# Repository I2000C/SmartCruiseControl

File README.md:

# SmartCruiseControl

SmartCruiseControl is an embedded ESP32 project that implements cruise control using CAN Bus data, with vehicle state monitoring and ELM327 command emulation for the **Smart forfour 454** car

## Description

The software runs on an ESP32 using the Arduino framework and focuses on:

- Reading CAN Bus frames from a Smart vehicle.
- Estimating speed, RPM, distance, fuel level, and other critical vehicle parameters.
- Cruise control with PID, button-based enable/disable, and throttle override handling.
- Basic ELM327 emulation for OBD-II `01xx` and `22xx` command responses.
- Cruise control status indication using an LED.

## Key features

- CAN Bus listen-only mode (`TWAI_MODE_LISTEN_ONLY`) at 500 kbps.
- Support for reading the following key CAN IDs:
  - `0x09E` - total distance
  - `0x200` - speed
  - `0x208` - brake intensity and extra speed data
  - `0x210` - accelerator pedal position
  - `0x308` - engine RPM
  - `0x408` - fuel level
  - `0x416` - battery voltage
  - `0x423` - door status
  - `0x608` - refrigerant temperature and fuel rate
- Cruise control state machine with:
  - `STATE_OFF`
  - `STATE_ACTIVE`
  - `STATE_OVERRIDE`
- ELM327 interface over `Serial` with basic `AT`, `01`, and `22` command handling.

## Project structure

- `platformio.ini` - PlatformIO configuration for ESP32.
- `src/main.cpp` - main entry point and FreeRTOS task setup.
- `include/` - constants, state definitions, and shared headers.
- `lib/` - modular libraries:
  - `can/` - CAN bus reading and decoding.
  - `cruise_control/` - cruise control logic.
  - `elm327/` - ELM327 emulation and OBD response handling.
  - `fuel_range_estimator/` - fuel range estimation.
  - `indicator_led/` - PWM LED status indicator.
  - `pid_controller/` - generic PID controller.
  - `speed_estimator/` - speed estimation from CAN frames.
  - `throttle/` - throttle output and override management.
  - `buttons/` - analog button reading and cruise control button detection.
- `doc/` - CAN Bus reverse engineering documentation.
- `test/` - PlatformIO testing notes and setup.

## Requirements

See `requirements.md` file for required software and hardware

## How to build

See `how-to-build.md` file to build software and hardware

## Usage

- The system starts by creating FreeRTOS tasks for CAN reception, CAN processing, and ELM327 emulation.
- The indicator LED shows cruise control status:
  - off = cruise control disabled
  - full brightness = cruise control active
  - fading = throttle override active
- Cruise control buttons support `SET`, `RESUME`, and `CANCEL`.
- Pressing the accelerator while cruise control is active transitions the system to `STATE_OVERRIDE`.

## Notes

- The project is designed for the Smart Forfour 454 (2006) model, as described at the beginning of `doc/CAN bus reverse engineering.md`.
- With the necessary modifications, it could be adapted to other vehicles that use CAN Bus, electronic throttle, and physical brake/clutch switches.
- The implementation is based on CAN data documented in `doc/CAN bus reverse engineering.md`.
- The ESP32 pinout reference image is available at `doc/ESP32 pinout.png` and is used under Creative Commons BY-NC-ND via www.mischianti.org.

## Inspirations

This project was inspired by:

- [esp32_cruise_control](https://github.com/successdt/esp32_cruise_control)
- [autocruise](https://github.com/SantiagoDelEstero/autocruise)
- [esp32-elm327-cruise-control](https://github.com/ipepe-oss/esp32-elm327-cruise-control)

## License

See the `LICENSE` file for the project license terms.

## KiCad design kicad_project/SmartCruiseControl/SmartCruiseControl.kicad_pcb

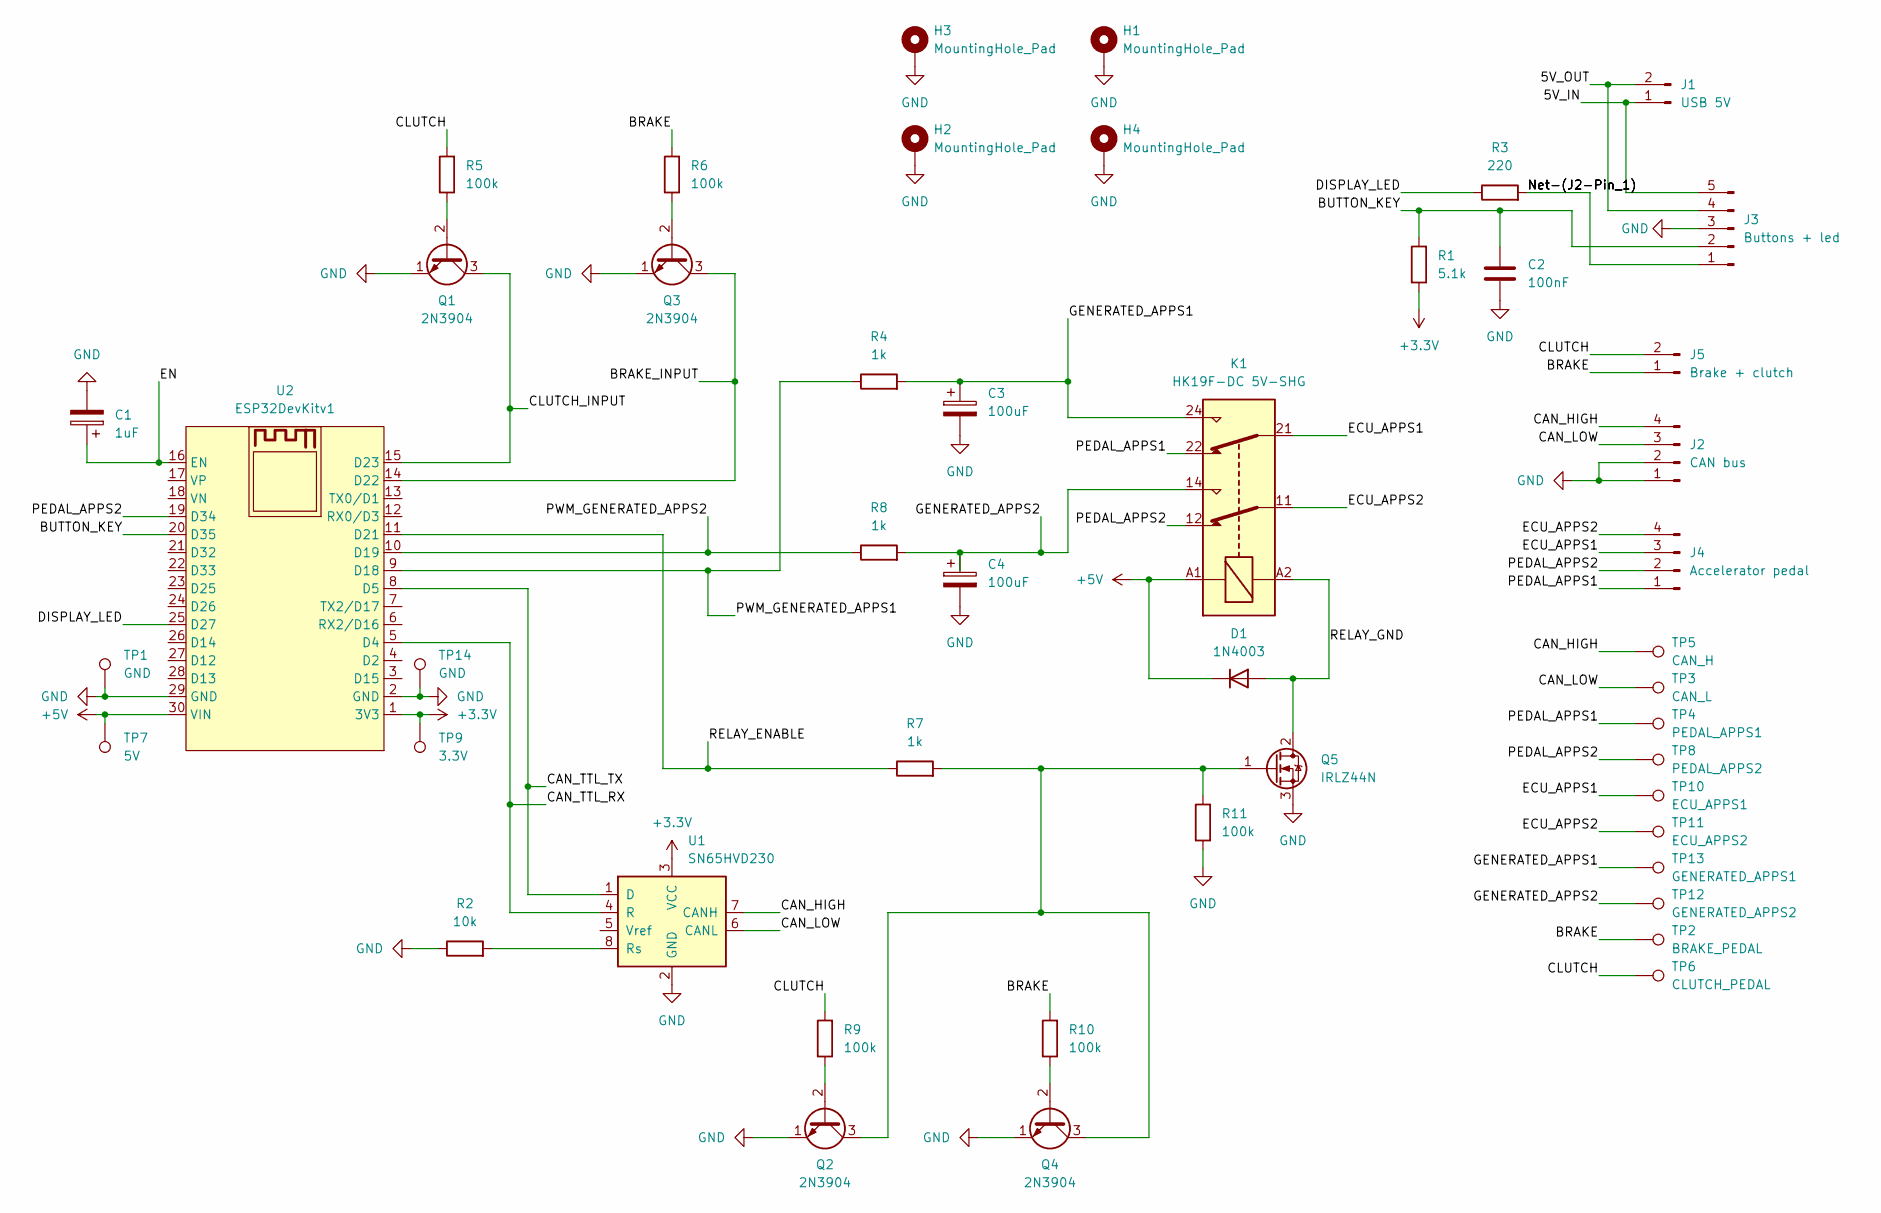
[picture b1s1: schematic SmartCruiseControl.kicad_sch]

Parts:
C1: 1uF; CP_Radial_D5.0mm_P2.00mm
C2: 100nF; C_Disc_D5.0mm_W2.5mm_P5.00mm
C3, C4: 100uF; CP_Radial_D5.0mm_P2.00mm
D1: 1N4003; D_DO-41_SOD81_P10.16mm_Horizontal
H1, H2, H3, H4: MountingHole_Pad; MountingHole_3.2mm_M3_Pad_Via
J1: USB 5V; JST_XH_B2B-XH-A_1x02_P2.50mm_Vertical
J2: CAN bus; JST_XH_B4B-XH-A_1x04_P2.50mm_Vertical
J3: Buttons + led; JST_XH_B5B-XH-A_1x05_P2.50mm_Vertical
J4: Accelerator pedal; JST_XH_B4B-XH-A_1x04_P2.50mm_Vertical
J5: Brake + clutch; JST_XH_B2B-XH-A_1x02_P2.50mm_Vertical
K1: HK19F-DC 5V-SHG; Relay_DPDT_Omron_G6A
Q1, Q2, Q3, Q4: 2N3904; TO-92_Inline
Q5: IRLZ44N; TO-220-3_Vertical
R1: 5.1k; R_Axial_DIN0207_L6.3mm_D2.5mm_P10.16mm_Horizontal
R2: 10k; R_Axial_DIN0207_L6.3mm_D2.5mm_P10.16mm_Horizontal
R3: 220; R_Axial_DIN0207_L6.3mm_D2.5mm_P10.16mm_Horizontal
R4, R7, R8: 1k; R_Axial_DIN0207_L6.3mm_D2.5mm_P10.16mm_Horizontal
R5, R6, R9, R10, R11: 100k; R_Axial_DIN0207_L6.3mm_D2.5mm_P10.16mm_Horizontal
TP1, TP14: GND; TestPoint_THTPad_2.0x2.0mm_Drill1.0mm
TP2: BRAKE_PEDAL; TestPoint_THTPad_D1.0mm_Drill0.5mm
TP3: CAN_L; TestPoint_THTPad_D1.0mm_Drill0.5mm
TP4: PEDAL_APPS1; TestPoint_THTPad_D1.0mm_Drill0.5mm
TP5: CAN_H; TestPoint_THTPad_D1.0mm_Drill0.5mm
TP6: CLUTCH_PEDAL; TestPoint_THTPad_D1.0mm_Drill0.5mm
TP7: 5V; TestPoint_THTPad_D2.0mm_Drill1.0mm
TP8: PEDAL_APPS2; TestPoint_THTPad_D1.0mm_Drill0.5mm
TP9: 3.3V; TestPoint_THTPad_D1.5mm_Drill0.7mm
TP10: ECU_APPS1; TestPoint_THTPad_D1.0mm_Drill0.5mm
TP11: ECU_APPS2; TestPoint_THTPad_D1.0mm_Drill0.5mm
TP12: GENERATED_APPS2; TestPoint_THTPad_D1.0mm_Drill0.5mm
TP13: GENERATED_APPS1; TestPoint_THTPad_D1.0mm_Drill0.5mm
U1: SN65HVD230; SOIC-8_3.9x4.9mm_P1.27mm
U2: ESP32DevKitv1

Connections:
+3.3V: R1.1, TP9.1 (1_1), U1.3 (VCC), U2.1 (3V3)
+5V: D1.1 (K), K1.A1, TP7.1 (1_1), U2.30 (VIN)
/5V_IN: J1.1, J3.5
/5V_OUT: J1.2, J3.4
/BRAKE: J5.1, R6.2, R10.2, TP2.1 (1_1)
/BRAKE_INPUT: Q3.3 (C), U2.14 (D22)
/BUTTON_KEY: C2.1, J3.2, R1.2, U2.20 (D35)
/CAN_HIGH: J2.4, TP5.1 (1_1), U1.7 (CANH)
/CAN_LOW: J2.3, TP3.1 (1_1), U1.6 (CANL)
/CAN_TTL_RX: U1.4 (R), U2.5 (D4)
/CAN_TTL_TX: U1.1 (D), U2.8 (D5)
/CLUTCH: J5.2, R5.2, R9.2, TP6.1 (1_1)
/CLUTCH_INPUT: Q1.3 (C), U2.15 (D23)
/DISPLAY_LED: R3.1, U2.25 (D27)
/ECU_APPS1: J4.3, K1.21, TP10.1 (1_1)
/ECU_APPS2: J4.4, K1.11, TP11.1 (1_1)
/EN: C1.1, U2.16 (EN)
/GENERATED_APPS1: C3.1, K1.24, R4.2, TP13.1 (1_1)
/GENERATED_APPS2: C4.1, K1.14, R8.2, TP12.1 (1_1)
/Net-(J2-Pin_1): J3.1, R3.2
/PEDAL_APPS1: J4.1, K1.22, TP4.1 (1_1)
/PEDAL_APPS2: J4.2, K1.12, TP8.1 (1_1), U2.19 (D34)
/PWM_GENERATED_APPS1: R4.1, U2.9 (D18)
/PWM_GENERATED_APPS2: R8.1, U2.10 (D19)
/RELAY_ENABLE: R7.1, U2.11 (D21)
/RELAY_GND: D1.2 (A), K1.A2, Q5.2 (D)
GND: C1.2, C2.2, C3.2, C4.2, H1.1 (1_1), H2.1 (1_1), H3.1 (1_1), H4.1 (1_1), J2.1, J2.2, J3.3, Q1.1 (E), Q2.1 (E), Q3.1 (E), Q4.1 (E), Q5.3 (S), R2.1, R11.1, TP1.1 (1_1), TP14.1 (1_1), U1.2 (GND), U2.2 (GND), U2.29 (GND)
unnamed: Q1.2 (B), R5.1
unnamed: Q2.2 (B), R9.1
unnamed: Q2.3 (C), Q4.3 (C), Q5.1 (G), R7.2, R11.2
unnamed: Q3.2 (B), R6.1
unnamed: Q4.2 (B), R10.1
unnamed: R2.2, U1.8 (Rs)

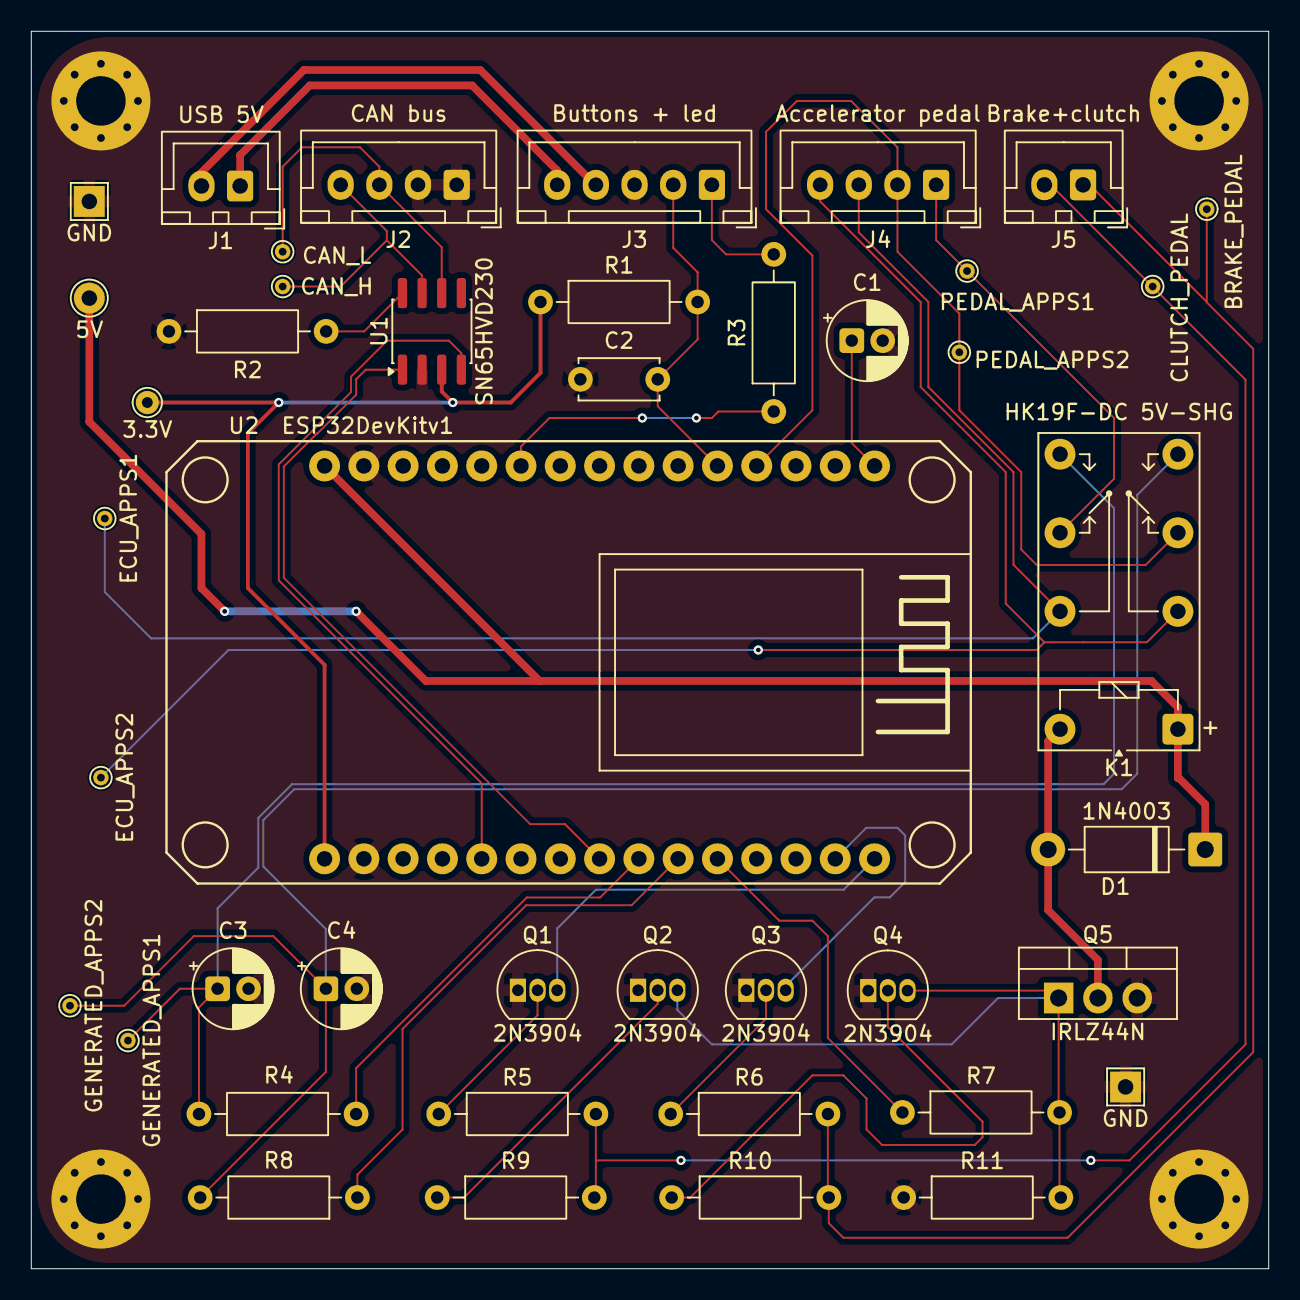
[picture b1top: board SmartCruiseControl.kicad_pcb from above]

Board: 2 copper layers, 80.0 x 80.0 mm, 47 parts (0 on the bottom side), 33 nets.

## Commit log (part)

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2026-05-25 Updated .gitignore
2026-05-25 Added initial PlatformIO files
2026-06-12 Added CAN module
2026-06-16 Added throttle module
2026-06-16 Added brake_clutch module
2026-06-16 Added Elm327 module
2026-06-16 Added indicator led module
2026-06-16 Added buttons module
2026-06-16 Added PIDController module
2026-06-16 Added main module
2026-06-17 Replaced enum by enum class
2026-06-17 Added cruise control module
2026-06-17 Updated platformio.ini
    Now uses C++17 and espressif32@7.0.1
2026-06-17 Fixed linage bug
2026-06-17 Fixed bug in can_reader
    computed data was being updated after a lot of times instead of refreshing every REFRESH_COMPUTED_DATA_TIME_MS
2026-06-17 Fixed bug in can_decoder
    Average speed was always 1
2026-06-17 Updated buttons module
2026-06-17 Added constrain to throttle and brake intensity values
2026-06-17 Fixed bugs in elm327.cpp
    - Now responses are sent correctly
    - Now pid is validated to be HEX using end pointer parameter of strtol()
2026-06-17 Added RPM_TIMEOUT_MS
2026-06-17 Updated ADC module
2026-06-17 Fixed bug in pid_controller (prevProcessValue was being used instead of _prevOutput)
2026-06-17 Replaced memory_order_release with memory_order_relaxed in ENTER_CRITICAL in can_decoder.h
2026-06-18 Removed bracke_clutch module and added relay detection logic to throttle module
2026-06-18 Added ESP32 pinout image
2026-06-18 Added CAN bus reverse engineering.md
2026-06-18 Added README.md
2026-06-18 Added throttle pedal documentation
2026-06-18 Added brake and clutch pedal switches documentation
2026-06-19 Removed unused constant SNAPSHOT_PERIOD_MS
2026-06-19 Added comments to functions and constants
2026-06-19 Added error check on init
2026-06-19 Added stack overflow check in main.cpp
2026-06-22 Now Serial0 is used by default
2026-06-22 Readded brake_clutch module
2026-06-23 Fixed bug when initializing indicator_led module
2026-06-23 Modified throttle, brake and clutch pins
2026-06-23 Updated brake-clutch example
2026-06-23 Fixed bug when responding to extended OBDII frames
2026-06-23 Updated Kp, Ki and Kd parameters
2026-06-24 Added kicad project
2026-06-24 Added kicad library as submodule
2026-06-24 Added kicad preview files
2026-06-24 Added requirements.md and how-to-build.md files
2026-06-25 Fixed incorrect values in ELM327 module
    Rpm and voltage were incorrect and speed was always 0
2026-06-25 Updated fuel_range_estimator and added new extra PID 0x22000B for the used fuel liters value
